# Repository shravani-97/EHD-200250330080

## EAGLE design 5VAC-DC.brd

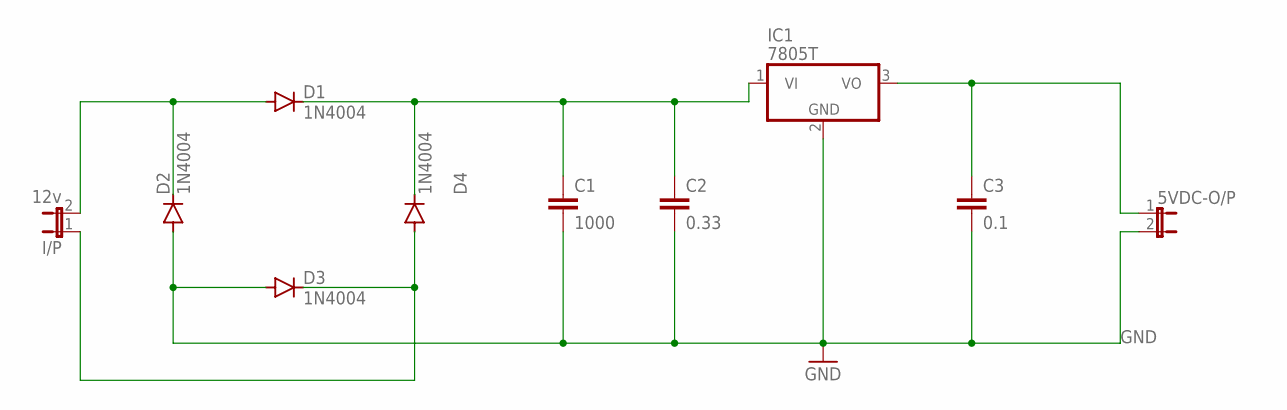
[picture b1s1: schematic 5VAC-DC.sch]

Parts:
5VDC-O/P: JP1E; JP1
C1: 1000; C2.5-3
C2: 0.33; C2.5-3
C3: 0.1; C2.5-3
D1, D2, D3, D4: 1N4004; DO41-10
I/P: 12v; JP1
IC1: 7805T; TO220H

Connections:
GND: 5VDC-O/P.2, C1.2, C2.2, C3.2, D2.A, D3.A, IC1.2 (GND)
unnamed: C1.1, C2.1, D1.C, D4.C, IC1.1 (VI)
unnamed: D3.C, D4.A, I/P.1
unnamed: D1.A, D2.C, I/P.2
unnamed: 5VDC-O/P.1, C3.1, IC1.3 (VO)

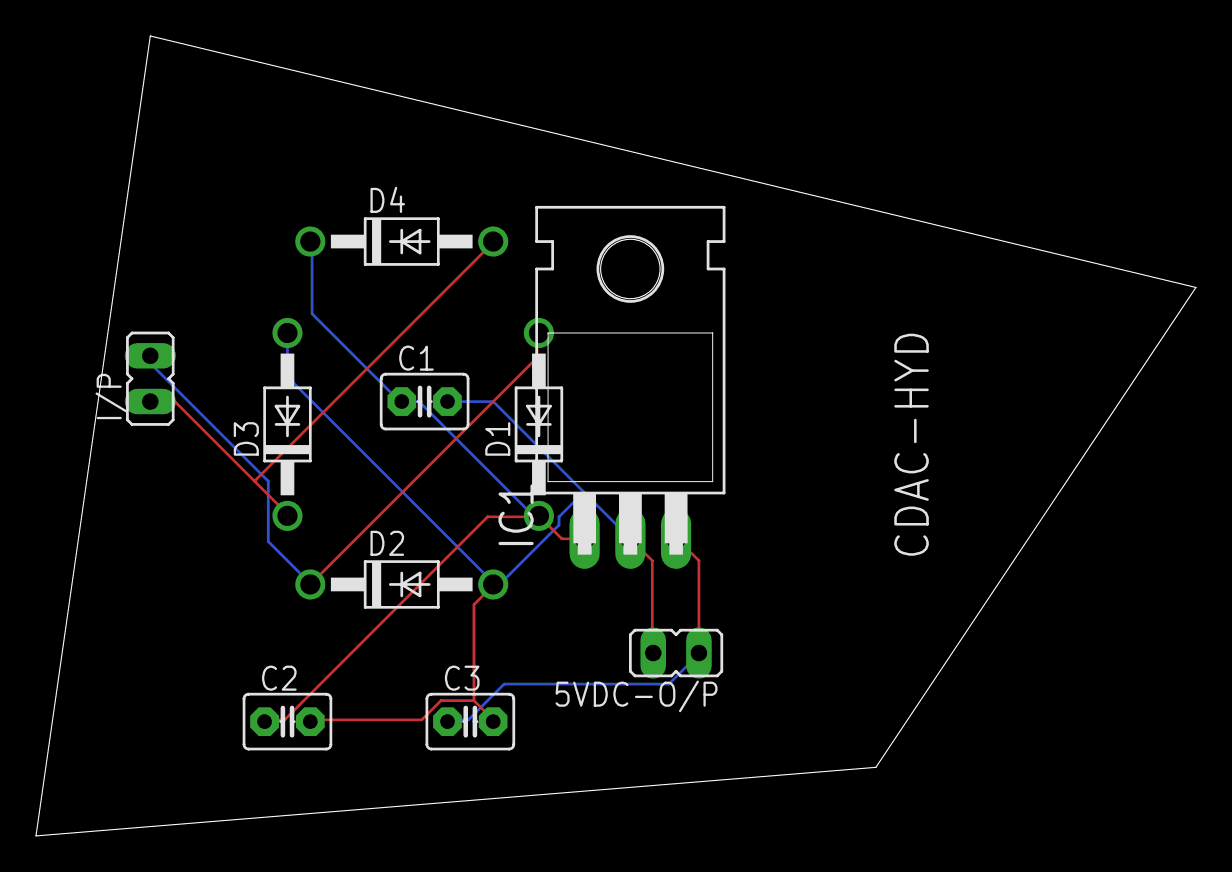
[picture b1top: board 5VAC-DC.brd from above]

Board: 2 copper layers, 64.4 x 44.4 mm, 10 parts (0 on the bottom side), 5 nets.
